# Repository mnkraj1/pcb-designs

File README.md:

# Simple PCB designs using Eagle
## Contents
1. Low Pass Filter
2. DC-DC convertor
3. SIPO

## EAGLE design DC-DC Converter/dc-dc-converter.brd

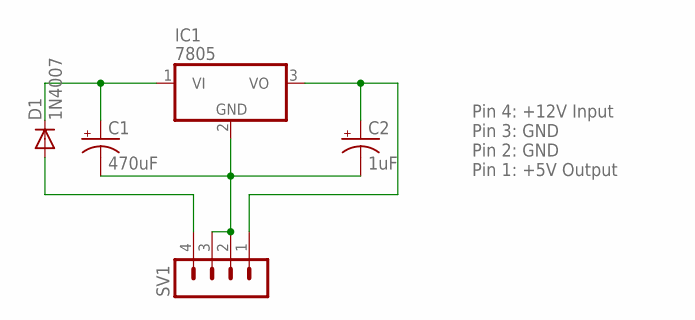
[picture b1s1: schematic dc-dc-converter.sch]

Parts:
C1: 470uF; B45181A
C2: 1uF; B45181A
D1: 1N4007; DO41-10
IC1: 7805; TO220V
SV1: MA04-1

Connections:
unnamed: C1.+, D1.C, IC1.1 (VI)
unnamed: D1.A, SV1.4
unnamed: C2.+, IC1.3 (VO), SV1.1
unnamed: C1.-, C2.-, IC1.2 (GND), SV1.2, SV1.3

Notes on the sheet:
Pin 4: +12V Input Pin 3: GND Pin 2: GND Pin 1: +5V Output

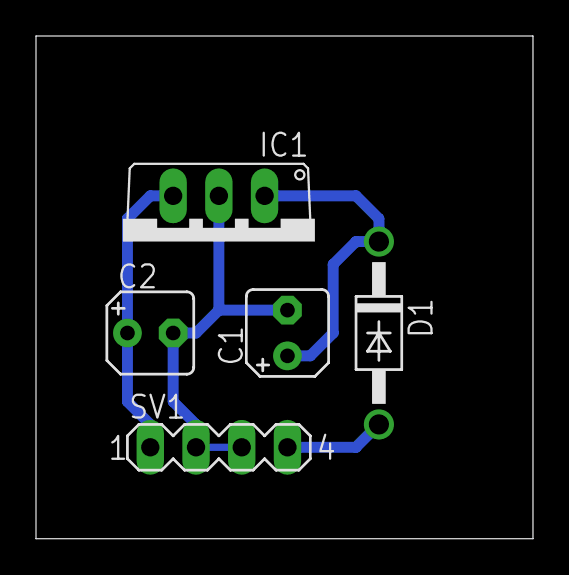
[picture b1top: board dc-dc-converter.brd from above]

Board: 2 copper layers, 27.6 x 27.9 mm, 5 parts (0 on the bottom side), 4 nets.

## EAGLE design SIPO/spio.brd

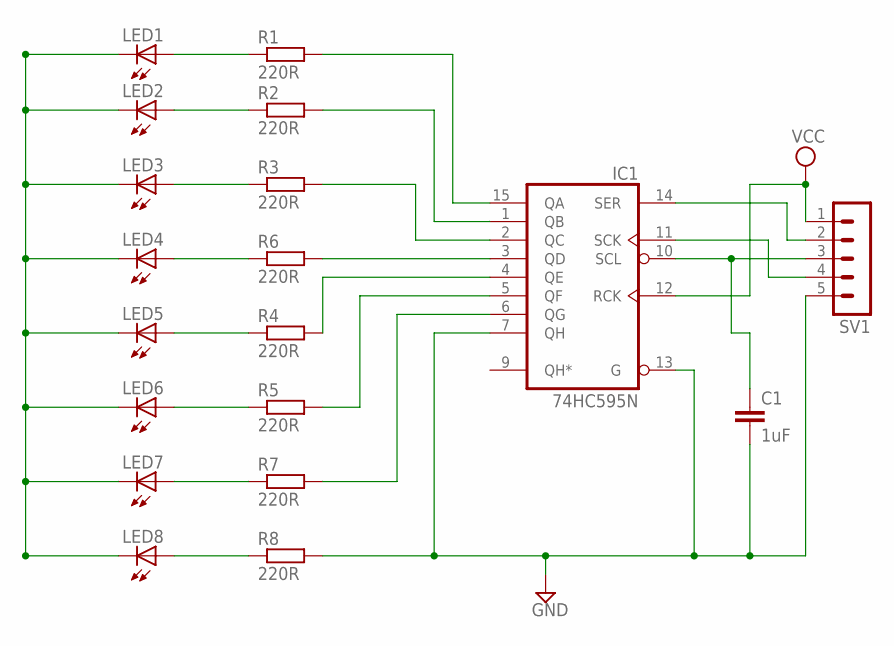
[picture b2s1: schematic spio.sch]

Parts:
C1: 1uF; C025-024X044
IC1: 74HC595N; DIL16
LED1, LED2, LED3, LED4, LED5, LED6, LED7, LED8: LED5MM
R1, R2, R3, R4, R5, R6, R7, R8: 220R; 0204V
SV1: MA05-1

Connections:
GND: C1.2, IC1.7 (QH), IC1.8 (GND), IC1.13 (G), R8.2, SV1.5
unnamed: LED1.A, R1.1
unnamed: LED2.A, R2.1
unnamed: LED3.A, R3.1
unnamed: LED4.A, R6.1
unnamed: LED5.A, R4.1
unnamed: LED6.A, R5.1
unnamed: LED7.A, R7.1
unnamed: LED8.A, R8.1
unnamed: LED1.K (C), LED2.K (C), LED3.K (C), LED4.K (C), LED5.K (C), LED6.K (C), LED7.K (C), LED8.K (C)
unnamed: IC1.2 (QC), R3.2
unnamed: IC1.3 (QD), R6.2
unnamed: IC1.4 (QE), R4.2
unnamed: IC1.5 (QF), R5.2
unnamed: IC1.6 (QG), R7.2
unnamed: IC1.11 (SCK), SV1.4
unnamed: IC1.15 (QA), R1.2
unnamed: IC1.1 (QB), R2.2
unnamed: IC1.14 (SER), SV1.2
unnamed: C1.1, IC1.10 (SCL), SV1.3
VCC: IC1.12 (RCK), IC1.16 (VCC), SV1.1

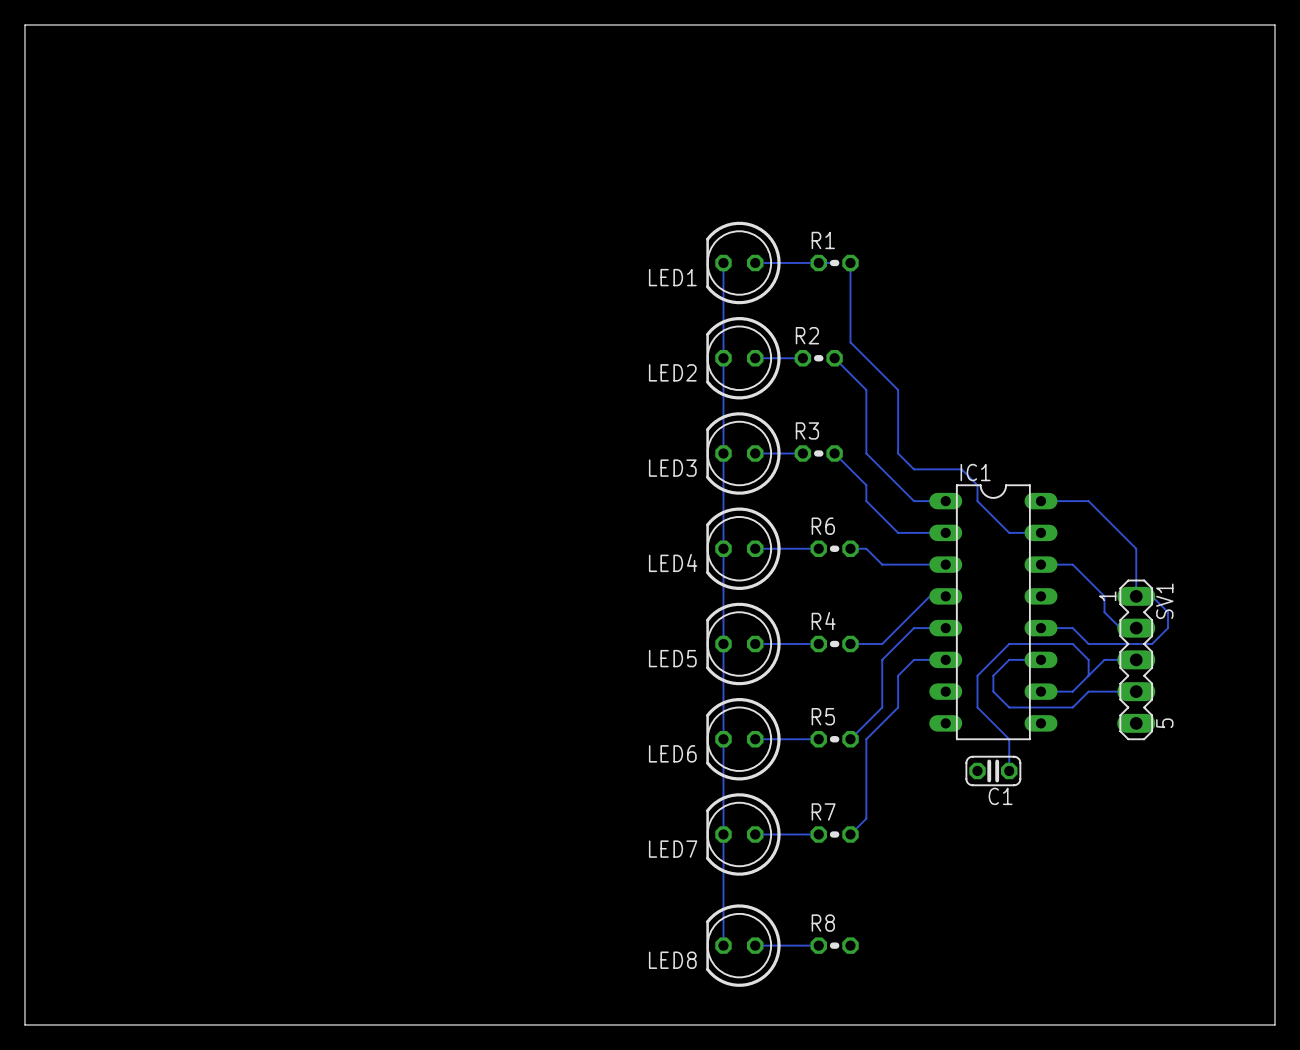
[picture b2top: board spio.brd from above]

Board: 2 copper layers, 100.0 x 80.0 mm, 19 parts (0 on the bottom side), 21 nets.

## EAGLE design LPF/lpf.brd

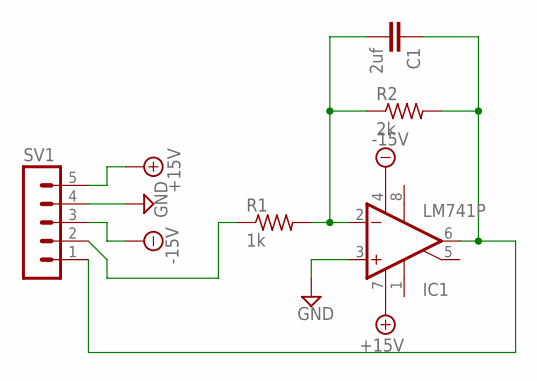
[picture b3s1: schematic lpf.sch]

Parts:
C1: 2uf; C025-024X044
IC1: LM741P; DIL08
R1: 1k; 0204V
R2: 2k; 0204V
SV1: MA05-1

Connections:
+15V: IC1.7 (V+), SV1.5
-15V: IC1.4 (V-), SV1.3
GND: IC1.3 (+IN), SV1.4
unnamed: C1.2, IC1.2 (-IN), R1.2, R2.1
unnamed: C1.1, IC1.6 (OUT), R2.2, SV1.1
unnamed: R1.1, SV1.2

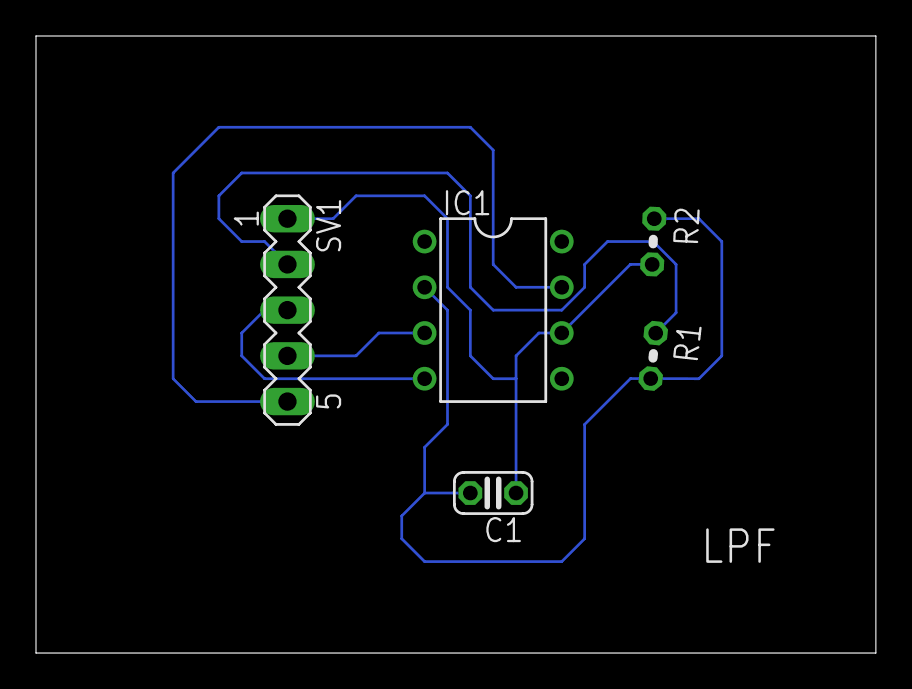
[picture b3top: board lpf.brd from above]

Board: 2 copper layers, 46.7 x 34.3 mm, 5 parts (0 on the bottom side), 6 nets.

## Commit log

2018-04-24 added LPF board design and schematic
2018-04-25 DC-DC convertor and SIPO schematic and design
2018-04-25 Readme updated
